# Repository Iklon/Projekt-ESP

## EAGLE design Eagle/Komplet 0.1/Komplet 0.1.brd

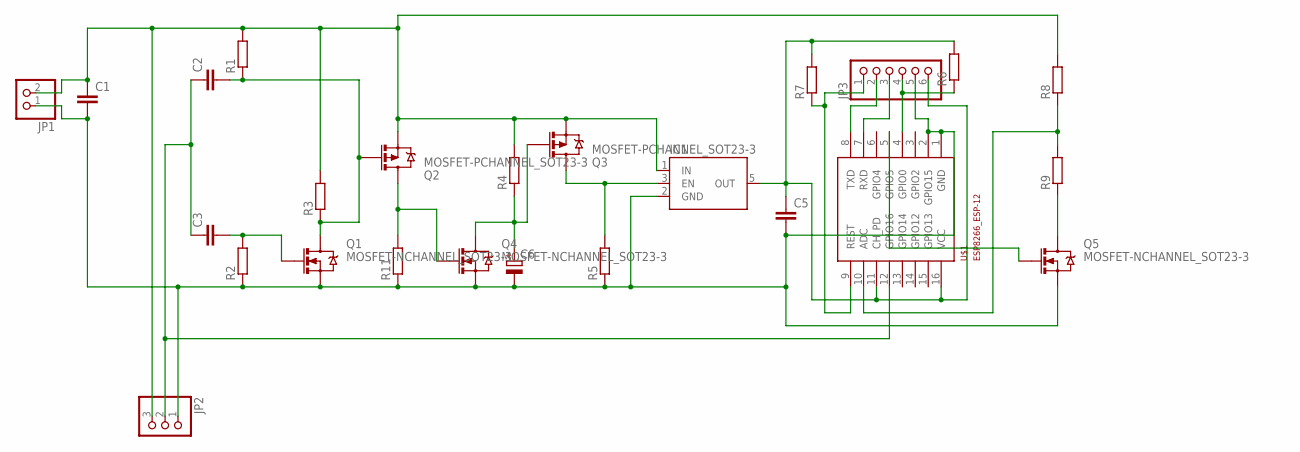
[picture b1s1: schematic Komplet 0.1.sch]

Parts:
C1, C2, C3, C5: C-EUC0805; C0805
C6: CPOL-EU153CLV-0807; 153CLV-0807
IC1: TLV700XX_DDC; SOT23-5
JP1: PINHD-1X02_2.54; 1X02
JP2: PINHD-1X03_2.54; 1X03
JP3: PINHD-1X06_2.54; 1X06
Q1, Q4, Q5: MOSFET-NCHANNEL_SOT23-3; SOT23-3
Q2, Q3: MOSFET-PCHANNEL_SOT23-3; SOT23-3
R1, R2, R3, R4, R5, R6, R7, R8, R9: R-EU_R0805; R0805
R11: R-EU_R1206; R1206
U$1: ESP8266_ESP-12; ESP8266-ESP12

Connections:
3V3: C5.1, IC1.5 (OUT), JP3.6, R6.2, R7.2, U$1.11 (CH_PD), U$1.16 (VCC)
GND: C1.2, C5.2, C6.-, IC1.2 (GND), JP1.1, JP2.1, JP3.5, Q1.2 (S), Q4.2 (S), Q5.2 (S), R2.1, R5.1, R11.1, U$1.1 (GND), U$1.2 (GPIO15)
unnamed: C6.+, Q3.1 (G), Q4.3 (D), R4.1
unnamed: C2.2, Q1.3 (D), Q2.1 (G), R1.1, R3.1
unnamed: Q2.3 (D), Q4.1 (G), R11.2
unnamed: C3.2, Q1.1 (G), R2.2
unnamed: Q5.1 (G), U$1.5 (GPIO5)
unnamed: JP3.4, R6.1, U$1.4 (GPIO0)
unnamed: JP3.3, U$1.7 (RXD)
unnamed: IC1.3 (EN), Q3.3 (D), R5.2
unnamed: JP3.2, U$1.8 (TXD)
unnamed: JP3.1, R7.1, U$1.9 (REST)
unnamed: Q5.3 (D), R9.1
unnamed: R8.1, R9.2, U$1.10 (ADC)
SIGNAL: C2.1, C3.1, JP2.2, U$1.12 (GPIO16)
V++: C1.1, IC1.1 (IN), JP1.2, JP2.3, Q2.2 (S), Q3.2 (S), R1.2, R3.2, R4.2, R8.2

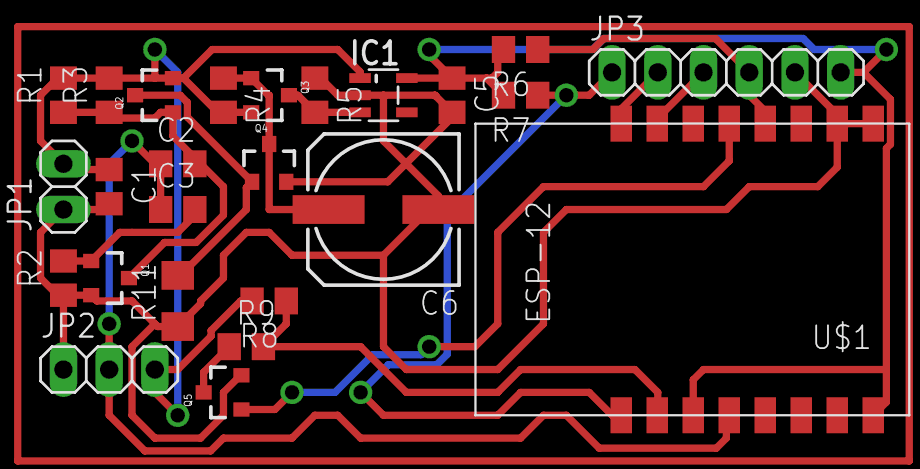
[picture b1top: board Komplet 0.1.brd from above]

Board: 2 copper layers, 25 parts (0 on the bottom side), 16 nets.

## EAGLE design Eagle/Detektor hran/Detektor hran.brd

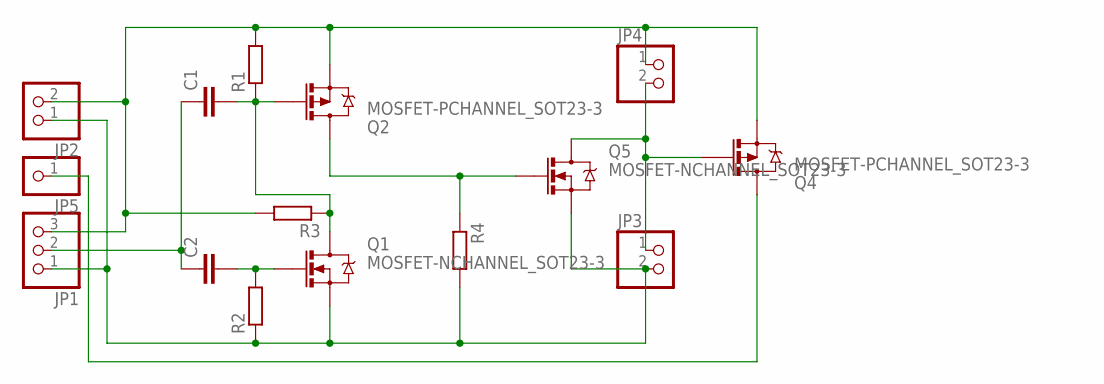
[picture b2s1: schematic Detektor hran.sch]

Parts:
C1, C2: C-EUC0805; C0805
JP1: PINHD-1X03_2.54; 1X03
JP2, JP3, JP4: PINHD-1X02_2.54; 1X02
JP5: PINHD-1X01_2.54-90°; 1X01/90
Q1, Q5: MOSFET-NCHANNEL_SOT23-3; SOT23-3
Q2, Q4: MOSFET-PCHANNEL_SOT23-3; SOT23-3
R1, R2, R3, R4: R-EU_R0805; R0805

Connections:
GND: JP1.1, JP2.1, JP3.2, Q1.2 (S), Q5.2 (S), R2.1, R4.2
unnamed: JP3.1, JP4.2, Q4.1 (G), Q5.3 (D)
unnamed: C1.1, C2.1, JP1.2
unnamed: C1.2, Q1.3 (D), Q2.1 (G), R1.1, R3.1
unnamed: C2.2, Q1.1 (G), R2.2
unnamed: JP5.1, Q4.3 (D)
unnamed: Q2.3 (D), Q5.1 (G), R4.1
V+: JP1.3, JP2.2, JP4.1, Q2.2 (S), Q4.2 (S), R1.2, R3.2

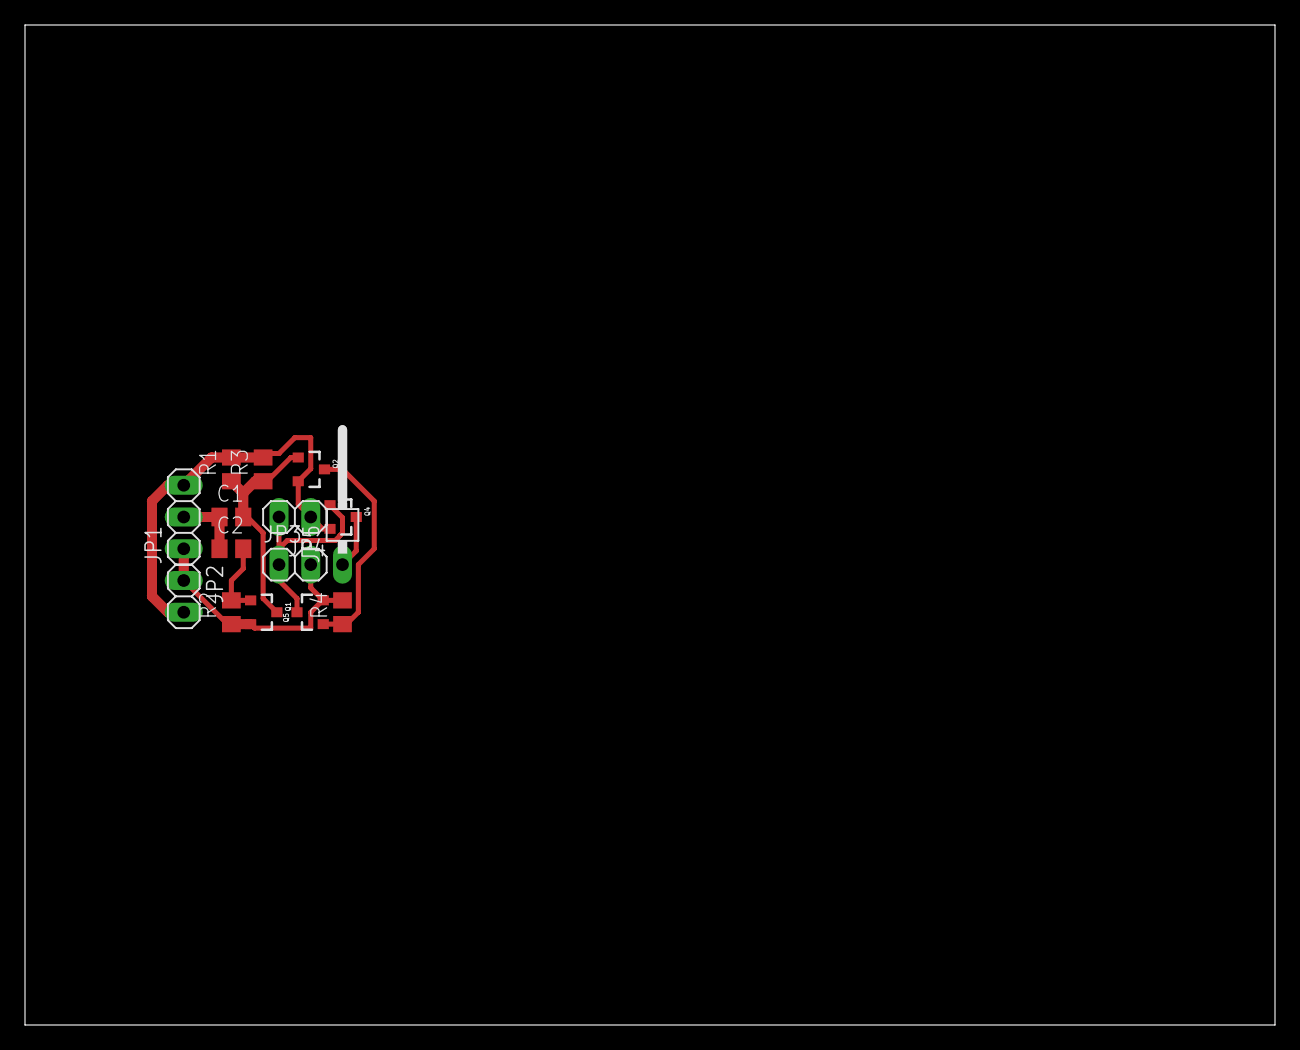
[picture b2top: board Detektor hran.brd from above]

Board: 2 copper layers, 100.0 x 80.0 mm, 15 parts (0 on the bottom side), 8 nets.

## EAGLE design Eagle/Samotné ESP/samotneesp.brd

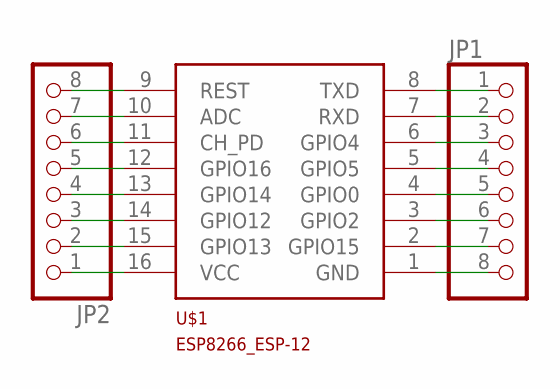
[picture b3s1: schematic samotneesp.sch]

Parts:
JP1, JP2: PINHD-1X8; 1X08
U$1: ESP8266_ESP-12; ESP8266-ESP12

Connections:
unnamed: JP2.8, U$1.9 (REST)
unnamed: JP2.7, U$1.10 (ADC)
unnamed: JP2.6, U$1.11 (CH_PD)
unnamed: JP2.5, U$1.12 (GPIO16)
unnamed: JP2.4, U$1.13 (GPIO14)
unnamed: JP2.3, U$1.14 (GPIO12)
unnamed: JP2.2, U$1.15 (GPIO13)
unnamed: JP2.1, U$1.16 (VCC)
unnamed: JP1.8, U$1.1 (GND)
unnamed: JP1.7, U$1.2 (GPIO15)
unnamed: JP1.6, U$1.3 (GPIO2)
unnamed: JP1.5, U$1.4 (GPIO0)
unnamed: JP1.4, U$1.5 (GPIO5)
unnamed: JP1.3, U$1.6 (GPIO4)
unnamed: JP1.2, U$1.7 (RXD)
unnamed: JP1.1, U$1.8 (TXD)

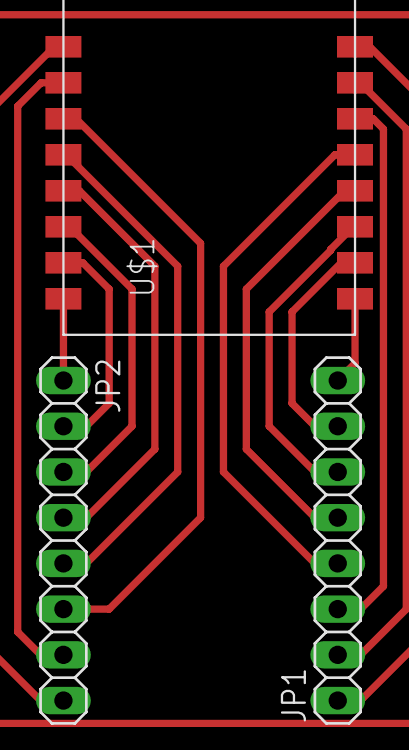
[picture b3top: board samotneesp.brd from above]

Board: 2 copper layers, 3 parts (0 on the bottom side), 16 nets.

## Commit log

2018-01-14 první commit
